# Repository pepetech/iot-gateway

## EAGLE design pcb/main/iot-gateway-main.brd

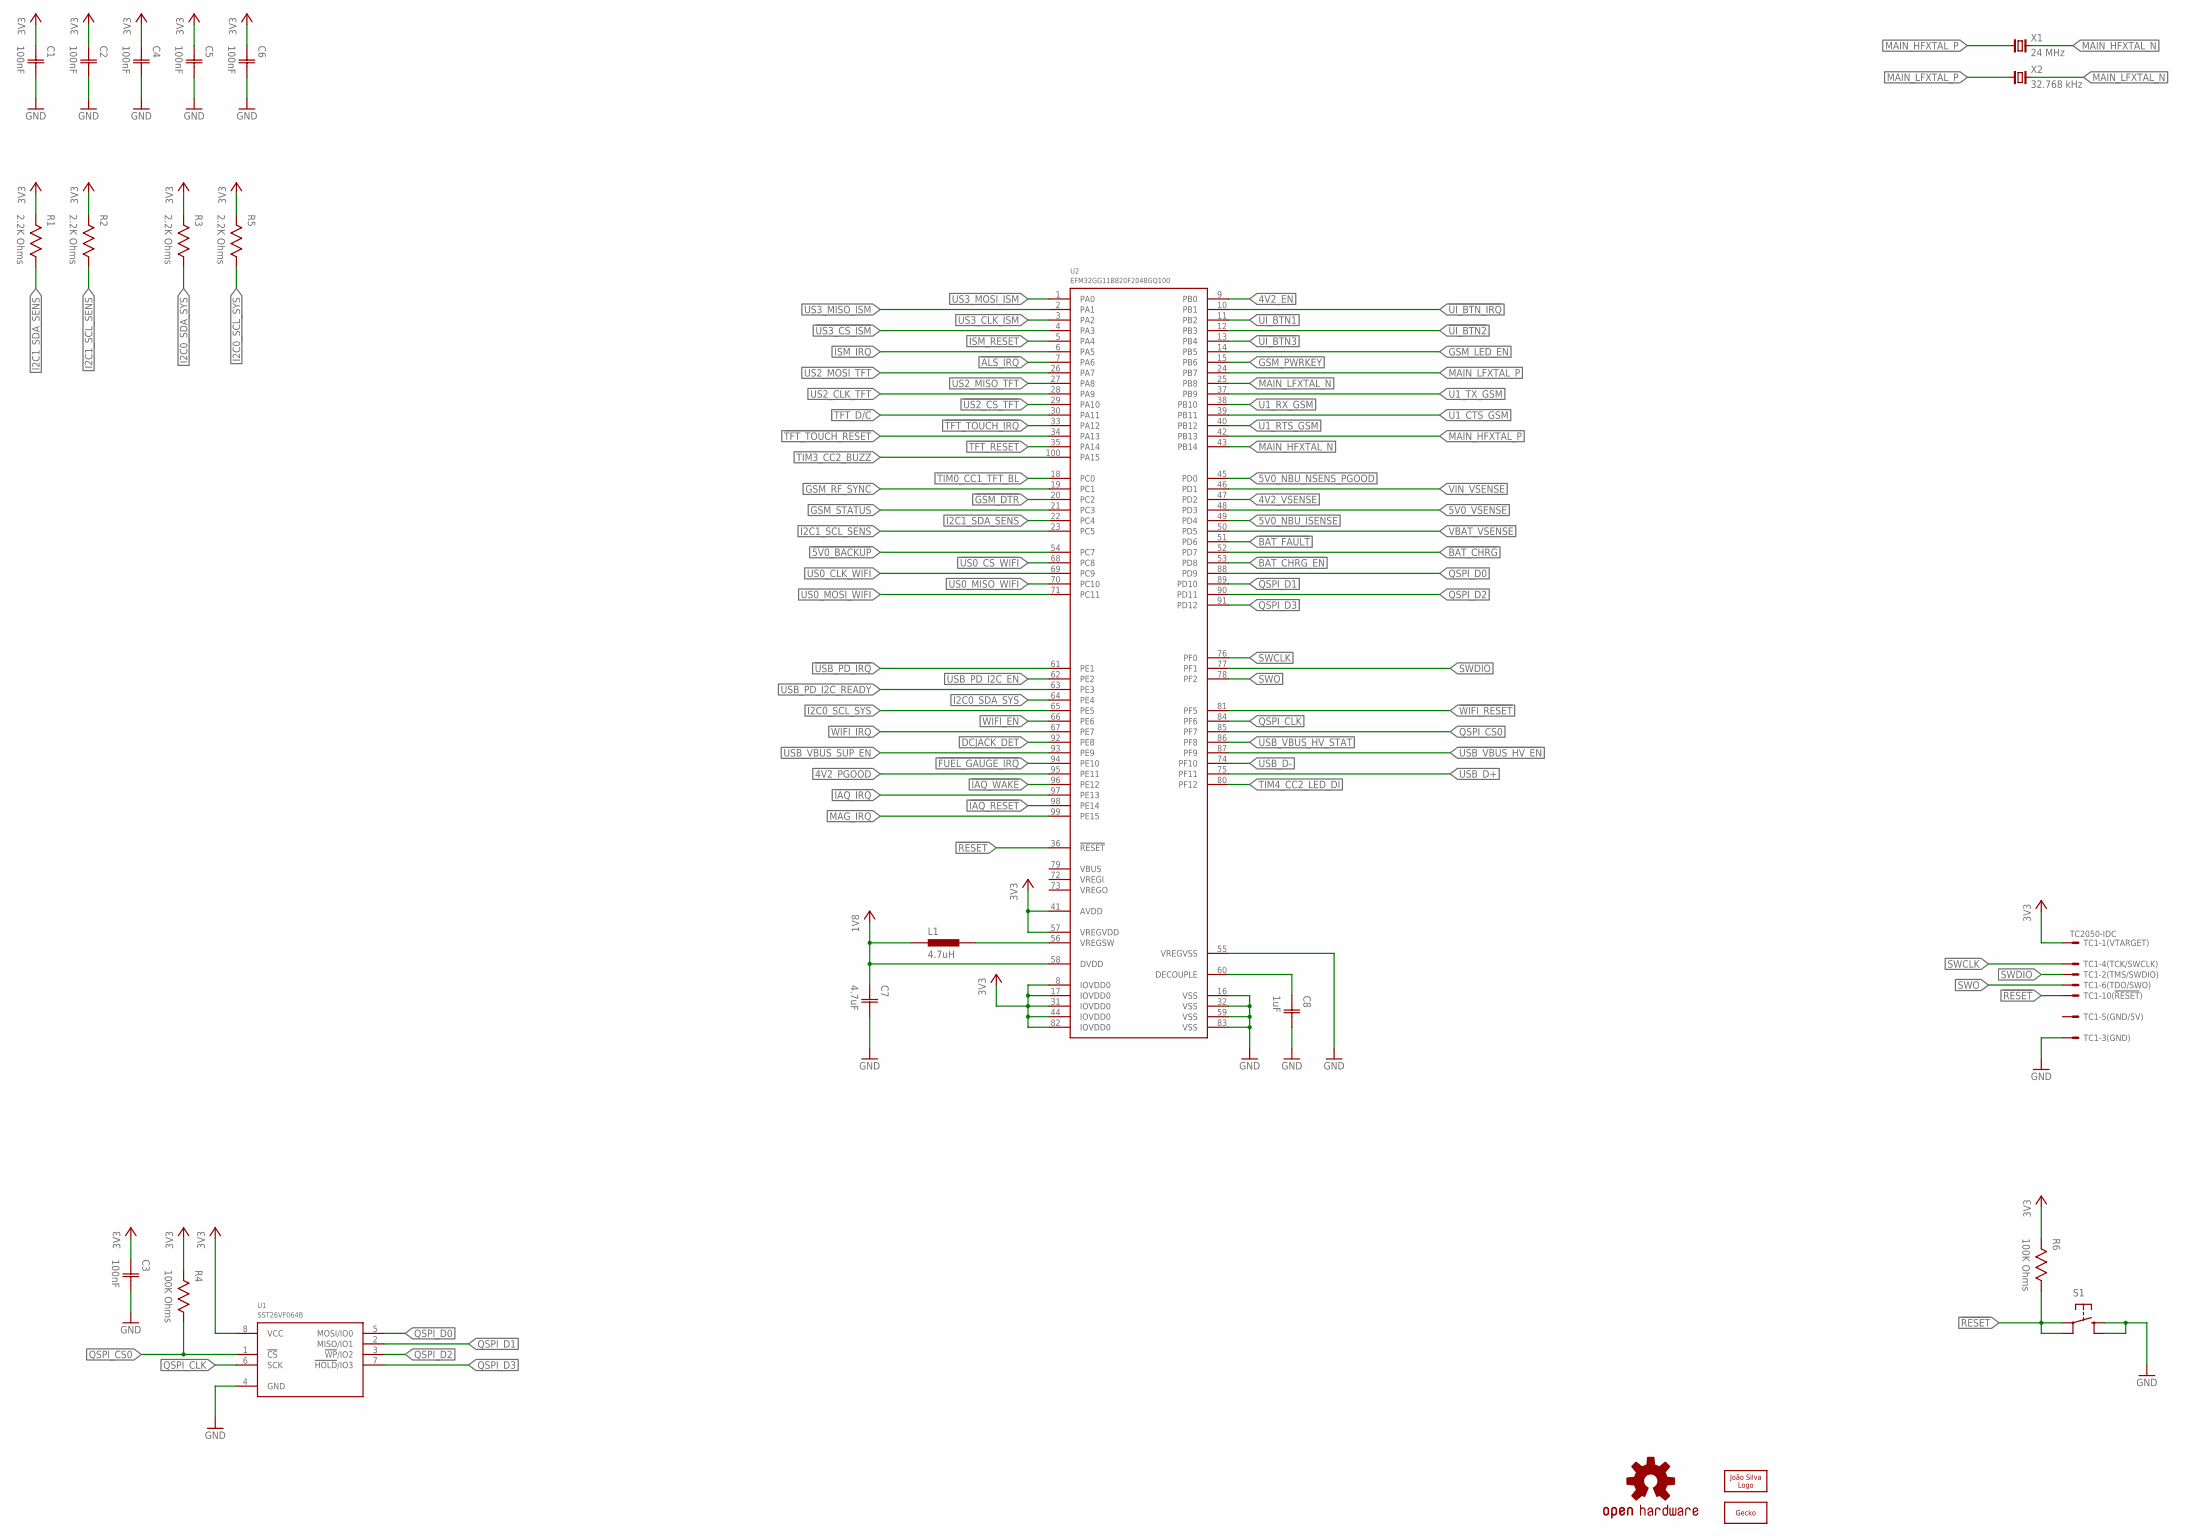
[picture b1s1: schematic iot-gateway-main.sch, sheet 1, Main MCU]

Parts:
C1, C2, C3, C4, C5, C6: 100nF; CAP0603
C7: 4.7uF; CAP0603
C8: 1uF; CAP0603
L1: 4.7uH; IND0603
LOGO1: OSHW-LOGOM; OSHW-LOGO-M
LOGO2: JS-10MM; JS_10MM
LOGO3: GECKO-14MM; GECKO_14MM
R1, R2, R3, R5: 2.2K Ohms; RES0603
R4, R6: 100K Ohms; RES0603
S1: TAC_SWITCHSMD; TAC_SW_SMD_RESET
TC1: TC2050-IDC
U1: SST26VF064B; WSOIC8
U2: EFM32GG11B820F2048GQ100; QFP100
X1: 24 MHz; 2-SMD-5032
X2: 32.768 kHz; 2-SMD-3215

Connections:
1V8: C7.1 (C1), L1.1, U2.58 (DVDD)
3V3: C1.1 (C1), C2.1 (C1), C3.1 (C1), C4.1 (C1), C5.1 (C1), C6.1 (C1), R1.2, R2.2, R3.2, R4.2, R5.2, R6.2, TC1.1, U1.8 (VCC), U2.8 (IOVDD0), U2.17 (IOVDD0), U2.31 (IOVDD0), U2.41 (AVDD), U2.44 (IOVDD0), U2.57 (VREGVDD), U2.82 (IOVDD0); also elsewhere on the board
4V2_EN: U2.9 (PB0); also elsewhere on the board
4V2_PGOOD: U2.95 (PE11); also elsewhere on the board
4V2_VSENSE: U2.47 (PD2); also elsewhere on the board
5V0_NBU_ISENSE: U2.49 (PD4); also elsewhere on the board
5V0_NBU_NSENS_PGOOD: U2.45 (PD0); also elsewhere on the board
5V0_VSENSE: U2.48 (PD3); also elsewhere on the board
!5V0_BACKUP: U2.54 (PC7); also elsewhere on the board
!ALS_IRQ: U2.7 (PA6); also elsewhere on the board
!BAT_CHRG: U2.52 (PD7); also elsewhere on the board
!BAT_CHRG_EN: U2.53 (PD8); also elsewhere on the board
!BAT_FAULT: U2.51 (PD6); also elsewhere on the board
!FUEL_GAUGE_IRQ: U2.94 (PE10); also elsewhere on the board
!GSM_DTR: U2.20 (PC2); also elsewhere on the board
!IAQ_IRQ: U2.97 (PE13); also elsewhere on the board
!IAQ_RESET: U2.98 (PE14); also elsewhere on the board
!IAQ_WAKE: U2.96 (PE12); also elsewhere on the board
!RESET: R6.1, S1.1, S1.2, TC1.10, U2.36 (!RESET)
!TFT_RESET: U2.35 (PA14); also elsewhere on the board
!TFT_TOUCH_IRQ: U2.33 (PA12); also elsewhere on the board
!TFT_TOUCH_RESET: U2.34 (PA13); also elsewhere on the board
!UI_BTN1: U2.11 (PB2); also elsewhere on the board
!UI_BTN2: U2.12 (PB3); also elsewhere on the board
!UI_BTN3: U2.13 (PB4); also elsewhere on the board
!UI_BTN_IRQ: U2.10 (PB1); also elsewhere on the board
!US0_CS_WIFI: U2.68 (PC8); also elsewhere on the board
!US2_CS_TFT: U2.29 (PA10); also elsewhere on the board
!US3_CS_ISM: U2.4 (PA3); also elsewhere on the board
!USB_PD_IRQ: U2.61 (PE1); also elsewhere on the board
!USB_VBUS_HV_EN: U2.87 (PF9); also elsewhere on the board
!WIFI_RESET: U2.81 (PF5); also elsewhere on the board
DCJACK_DET: U2.92 (PE8); also elsewhere on the board
GND: C1.2 (C2), C2.2 (C2), C3.2 (C2), C4.2 (C2), C5.2 (C2), C6.2 (C2), C7.2 (C2), C8.2 (C2), S1.3, S1.4, TC1.3, U1.4 (GND), U2.16 (VSS), U2.32 (VSS), U2.55 (VREGVSS), U2.59 (VSS), U2.83 (VSS); also elsewhere on the board
GSM_LED_EN: U2.14 (PB5); also elsewhere on the board
GSM_PWRKEY: U2.15 (PB6); also elsewhere on the board
GSM_RF_SYNC: U2.19 (PC1); also elsewhere on the board
GSM_STATUS: U2.21 (PC3); also elsewhere on the board
I2C0_SCL_SYS: R5.1, U2.65 (PE5); also elsewhere on the board
I2C0_SDA_SYS: R3.1, U2.64 (PE4); also elsewhere on the board
I2C1_SCL_SENS: R2.1, U2.23 (PC5); also elsewhere on the board
I2C1_SDA_SENS: R1.1, U2.22 (PC4); also elsewhere on the board
ISM_IRQ: U2.6 (PA5); also elsewhere on the board
ISM_RESET: U2.5 (PA4); also elsewhere on the board
MAG_IRQ: U2.99 (PE15); also elsewhere on the board
MAIN_HFXTAL_N: U2.43 (PB14), X1.2
MAIN_HFXTAL_P: U2.42 (PB13), X1.1
MAIN_LFXTAL_N: U2.25 (PB8), X2.2
MAIN_LFXTAL_P: U2.24 (PB7), X2.1
MAIN_VDD_CORE: C8.1 (C1), U2.60 (DECOUPLE)
MAIN_VREG_SW: L1.2, U2.56 (VREGSW)
QSPI_CLK: U1.6 (SCK), U2.84 (PF6)
QSPI_CS0: R4.1, U1.1 (!CS!), U2.85 (PF7)
QSPI_D0: U1.5 (MOSI/IO0), U2.88 (PD9)
QSPI_D1: U1.2 (MISO/IO1), U2.89 (PD10)
QSPI_D2: U1.3 (!WP!/IO2), U2.90 (PD11)
QSPI_D3: U1.7 (!HOLD!/IO3), U2.91 (PD12)
SWCLK: TC1.4, U2.76 (PF0)
SWDIO: TC1.2, U2.77 (PF1)
SWO: TC1.6, U2.78 (PF2)
TFT_D/!C!: U2.30 (PA11); also elsewhere on the board
TIM0_CC1_TFT_BL: U2.18 (PC0); also elsewhere on the board
TIM3_CC2_BUZZ: U2.100 (PA15); also elsewhere on the board
TIM4_CC2_LED_DI: U2.80 (PF12); also elsewhere on the board
U1_CTS_GSM: U2.39 (PB11); also elsewhere on the board
U1_RTS_GSM: U2.40 (PB12); also elsewhere on the board
U1_RX_GSM: U2.38 (PB10); also elsewhere on the board
U1_TX_GSM: U2.37 (PB9); also elsewhere on the board
US0_CLK_WIFI: U2.69 (PC9); also elsewhere on the board
US0_MISO_WIFI: U2.70 (PC10); also elsewhere on the board
US0_MOSI_WIFI: U2.71 (PC11); also elsewhere on the board
US2_CLK_TFT: U2.28 (PA9); also elsewhere on the board
US2_MISO_TFT: U2.27 (PA8); also elsewhere on the board
US2_MOSI_TFT: U2.26 (PA7); also elsewhere on the board
US3_CLK_ISM: U2.3 (PA2); also elsewhere on the board
US3_MISO_ISM: U2.2 (PA1); also elsewhere on the board
US3_MOSI_ISM: U2.1 (PA0); also elsewhere on the board
USB_D+: U2.75 (PF11); also elsewhere on the board
USB_D-: U2.74 (PF10); also elsewhere on the board
USB_PD_I2C_EN: U2.62 (PE2); also elsewhere on the board
USB_PD_I2C_READY: U2.63 (PE3); also elsewhere on the board
USB_VBUS_HV_STAT: U2.86 (PF8); also elsewhere on the board
USB_VBUS_SUP_EN: U2.93 (PE9); also elsewhere on the board
VBAT_VSENSE: U2.50 (PD5); also elsewhere on the board
VIN_VSENSE: U2.46 (PD1); also elsewhere on the board
WIFI_EN: U2.66 (PE6); also elsewhere on the board
WIFI_IRQ: U2.67 (PE7); also elsewhere on the board

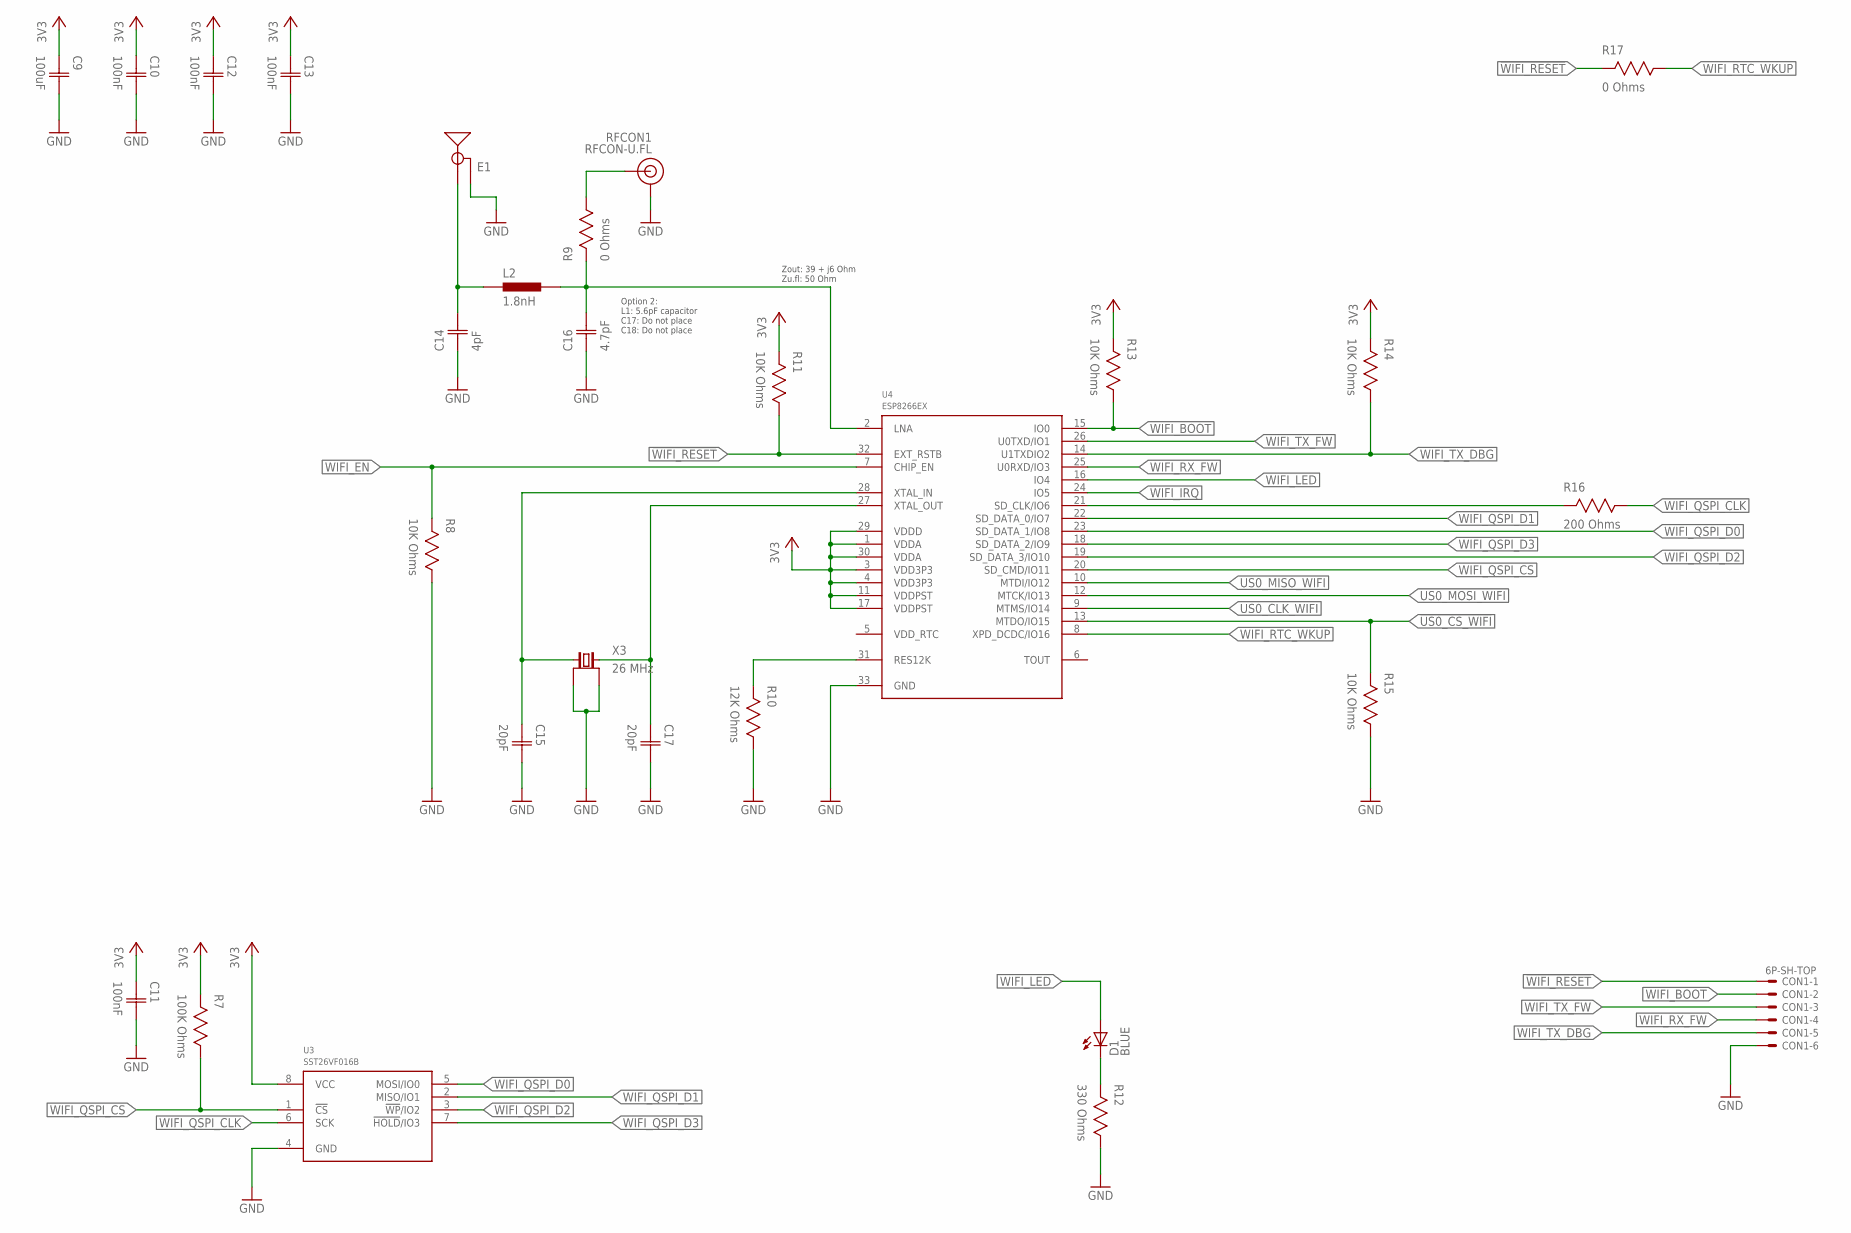
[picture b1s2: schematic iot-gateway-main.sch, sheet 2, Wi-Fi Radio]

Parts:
C9: 100uF; CAP1206
C10, C11, C12, C13: 100nF; CAP0603
C14: 4pF; CAP0603
C15, C17: 20pF; CAP0603
C16: 4.7pF; CAP0603
CON1: 6P-SH-TOP; SH-06-TOP
D1: BLUE; 1206_REV
E1: 2.4GHZTRACE-15.2MM; TRACE_ANTENNA_2.4GHZ_15.2MM
L2: 1.8nH; IND0603
R7: 100K Ohms; RES0603
R8, R11, R13, R14, R15: 10K Ohms; RES0603
R9, R17: 0 Ohms; RES0603
R10: 12K Ohms; RES0603
R12: 330 Ohms; RES0603
R16: 200 Ohms; RES0603
RFCON1: RFCON-U.FL; U.FL
U3: SST26VF016B; WSOIC8
U4: ESP8266EX; QFN32
X3: 26 MHz; 4-SMD-3225

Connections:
3V3: C9.1 (C1), C10.1 (C1), C11.1 (C1), C12.1 (C1), C13.1 (C1), R7.2, R11.2, R13.2, R14.2, U3.8 (VCC), U4.1 (VDDA), U4.3 (VDD3P3), U4.4 (VDD3P3), U4.11 (VDDPST), U4.17 (VDDPST), U4.29 (VDDD), U4.30 (VDDA); also elsewhere on the board
!US0_CS_WIFI: R15.2, U4.13 (MTDO/IO15); also elsewhere on the board
!WIFI_RESET: CON1.1, R11.1, R17.2, U4.32 (EXT_RSTB); also elsewhere on the board
GND: C9.2 (C2), C10.2 (C2), C11.2 (C2), C12.2 (C2), C13.2 (C2), C14.1 (C1), C15.2 (C2), C16.1 (C1), C17.2 (C2), CON1.6, E1.GND, R8.1, R10.1, R12.1, R15.1, RFCON1.P$1 (GND), RFCON1.P$2 (GND), U3.4 (GND), U4.33 (GND), X3.1 (GND), X3.3 (GND); also elsewhere on the board
unnamed: D1.C, R12.2
US0_CLK_WIFI: U4.9 (MTMS/IO14); also elsewhere on the board
US0_MISO_WIFI: U4.10 (MTDI/IO12); also elsewhere on the board
US0_MOSI_WIFI: U4.12 (MTCK/IO13); also elsewhere on the board
WIFI_ANT: C16.2 (C2), L2.2, R9.2, U4.2 (LNA)
WIFI_ANT_EXT: R9.1, RFCON1.P$3 (SIGNAL)
WIFI_ANT_FILT: C14.2 (C2), E1.ANT (SIGNAL), L2.1
WIFI_BIAS: R10.2, U4.31 (RES12K)
WIFI_BOOT: CON1.2, R13.1, U4.15 (IO0)
WIFI_EN: R8.2, U4.7 (CHIP_EN); also elsewhere on the board
WIFI_IRQ: U4.24 (IO5); also elsewhere on the board
WIFI_LED: D1.A, U4.16 (IO4)
WIFI_QSPI_CLK: R16.1, U3.6 (SCK)
WIFI_QSPI_CLK_FILT: R16.2, U4.21 (SD_CLK/IO6)
WIFI_QSPI_CS: R7.1, U3.1 (!CS!), U4.20 (SD_CMD/IO11)
WIFI_QSPI_D0: U3.5 (MOSI/IO0), U4.23 (SD_DATA_1/IO8)
WIFI_QSPI_D1: U3.2 (MISO/IO1), U4.22 (SD_DATA_0/IO7)
WIFI_QSPI_D2: U3.3 (!WP!/IO2), U4.19 (SD_DATA_3/IO10)
WIFI_QSPI_D3: U3.7 (!HOLD!/IO3), U4.18 (SD_DATA_2/IO9)
WIFI_RTC_WKUP: R17.1, U4.8 (XPD_DCDC/IO16)
WIFI_RX_FW: CON1.4, U4.25 (U0RXD/IO3)
WIFI_TX_DBG: CON1.5, R14.1, U4.14 (U1TXDIO2)
WIFI_TX_FW: CON1.3, U4.26 (U0TXD/IO1)
WIFI_XTAL_IN: C15.1 (C1), U4.28 (XTAL_IN), X3.2 (1)
WIFI_XTAL_OUT: C17.1 (C1), U4.27 (XTAL_OUT), X3.4 (2)

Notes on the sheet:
Option 2: L1: 5.6pF capacitor C17: Do not place C18: Do not place
Zout: 39 + j6 Ohm Zu.fl: 50 Ohm

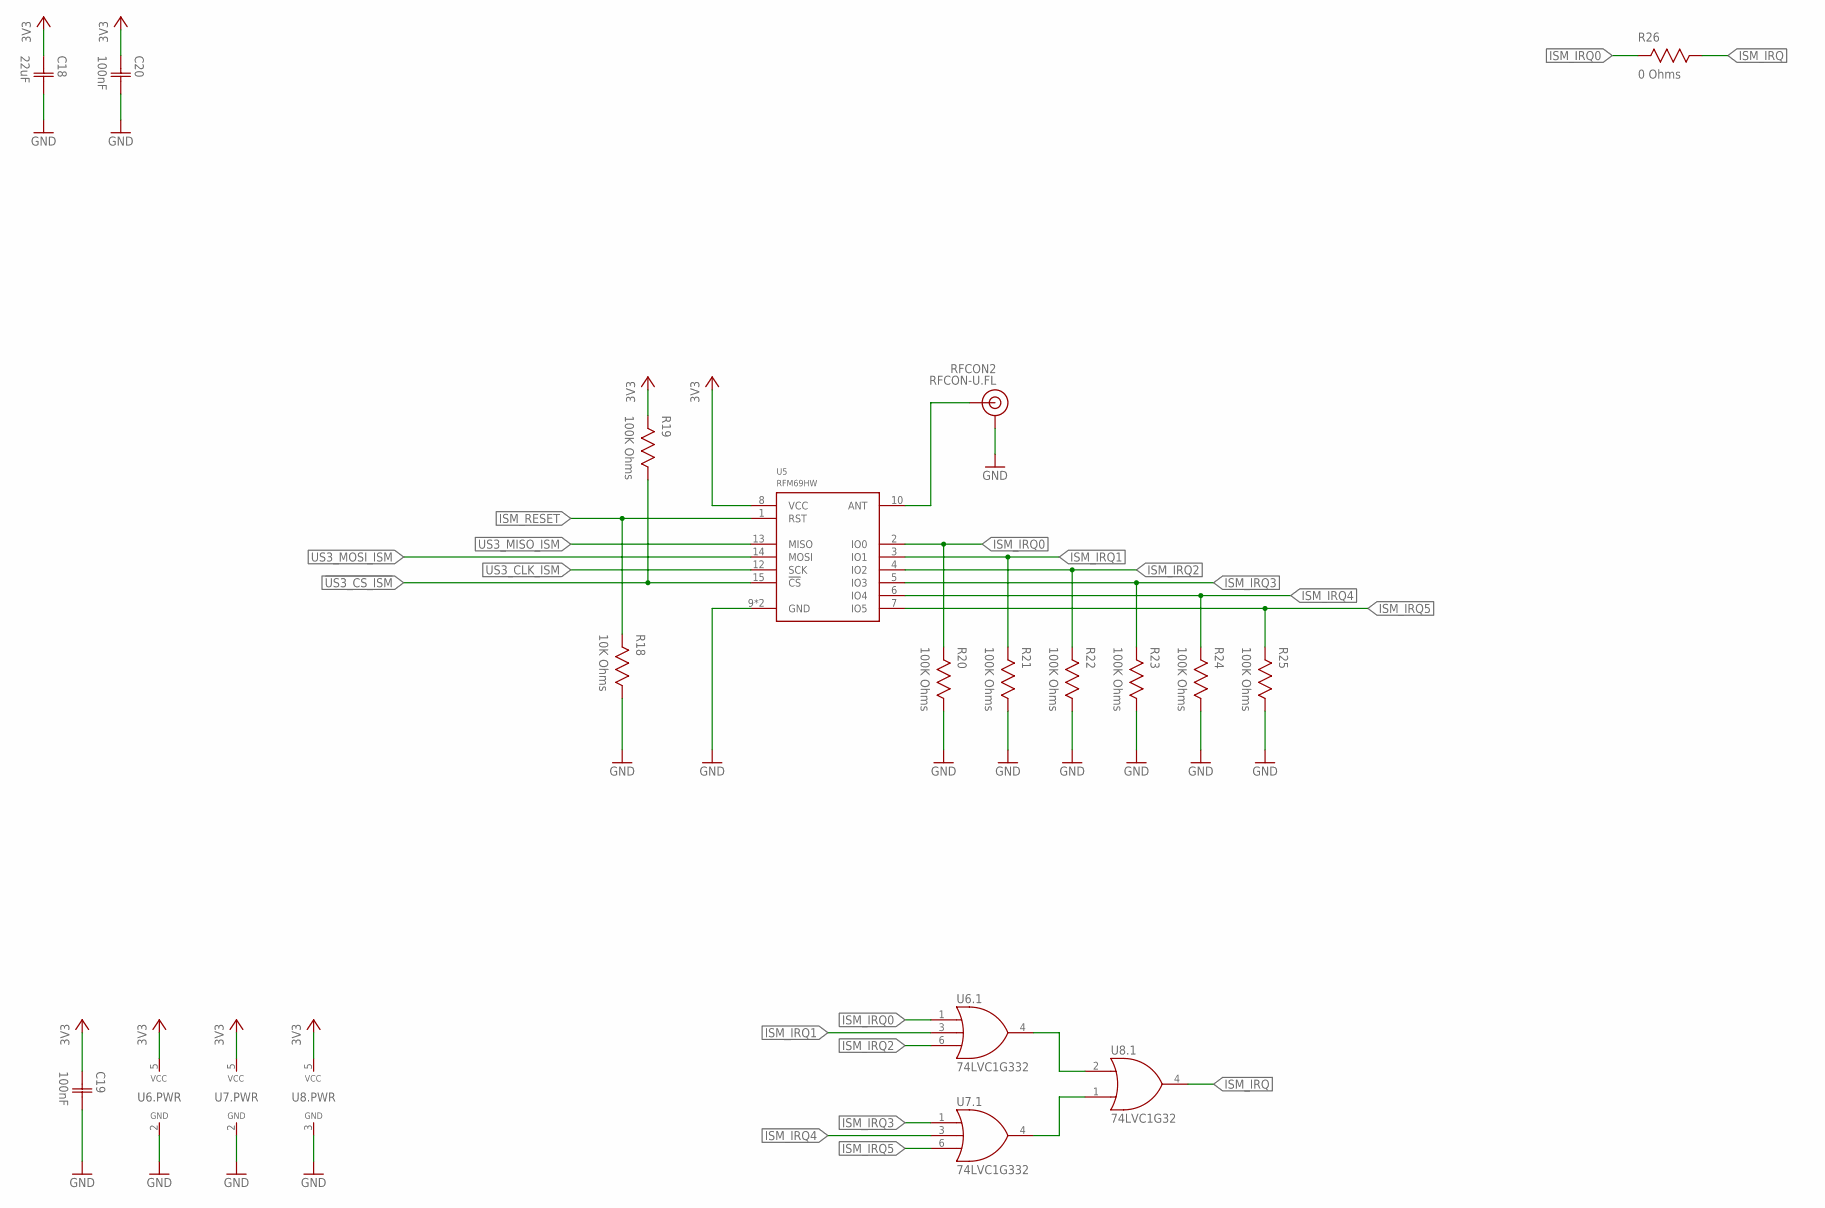
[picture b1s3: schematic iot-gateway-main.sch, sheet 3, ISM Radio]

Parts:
C18: 22uF; CAP1206
C19, C20: 100nF; CAP0603
R18: 10K Ohms; RES0603
R19, R20, R21, R22, R23, R24, R25: 100K Ohms; RES0603
R26: 0 Ohms; RES0603
RFCON2: RFCON-U.FL; U.FL
U5: RFM69HW; RFM69XW-XXXS2
U6, U7: 74LVC1G332; SC70-6
U8: 74LVC1G32; SC70-5

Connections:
3V3: C18.1 (C1), C19.1 (C1), C20.1 (C1), R19.2, U5.8 (VCC), U6.5 (VCC), U7.5 (VCC), U8.5 (VCC); also elsewhere on the board
!US3_CS_ISM: R19.1, U5.15 (!CS); also elsewhere on the board
GND: C18.2 (C2), C19.2 (C2), C20.2 (C2), R18.1, R20.1, R21.1, R22.1, R23.1, R24.1, R25.1, RFCON2.P$1 (GND), RFCON2.P$2 (GND), U5.9 (GND), U5.11 (GND), U6.2 (GND), U7.2 (GND), U8.3 (GND); also elsewhere on the board
ISM_IRQ: R26.1, U8.4 (Y); also elsewhere on the board
ISM_IRQ0: R20.2, R26.2, U5.2 (IO0), U6.1 (A)
ISM_IRQ1: R21.2, U5.3 (IO1), U6.3 (B)
ISM_IRQ2: R22.2, U5.4 (IO2), U6.6 (C)
ISM_IRQ3: R23.2, U5.5 (IO3), U7.1 (A)
ISM_IRQ4: R24.2, U5.6 (IO4), U7.3 (B)
ISM_IRQ5: R25.2, U5.7 (IO5), U7.6 (C)
ISM_IRQ012: U6.4 (Y), U8.2 (A)
ISM_IRQ345: U7.4 (Y), U8.1 (B)
ISM_RESET: R18.2, U5.1 (RST); also elsewhere on the board
unnamed: RFCON2.P$3 (SIGNAL), U5.10 (ANT)
US3_CLK_ISM: U5.12 (SCK); also elsewhere on the board
US3_MISO_ISM: U5.13 (MISO); also elsewhere on the board
US3_MOSI_ISM: U5.14 (MOSI); also elsewhere on the board

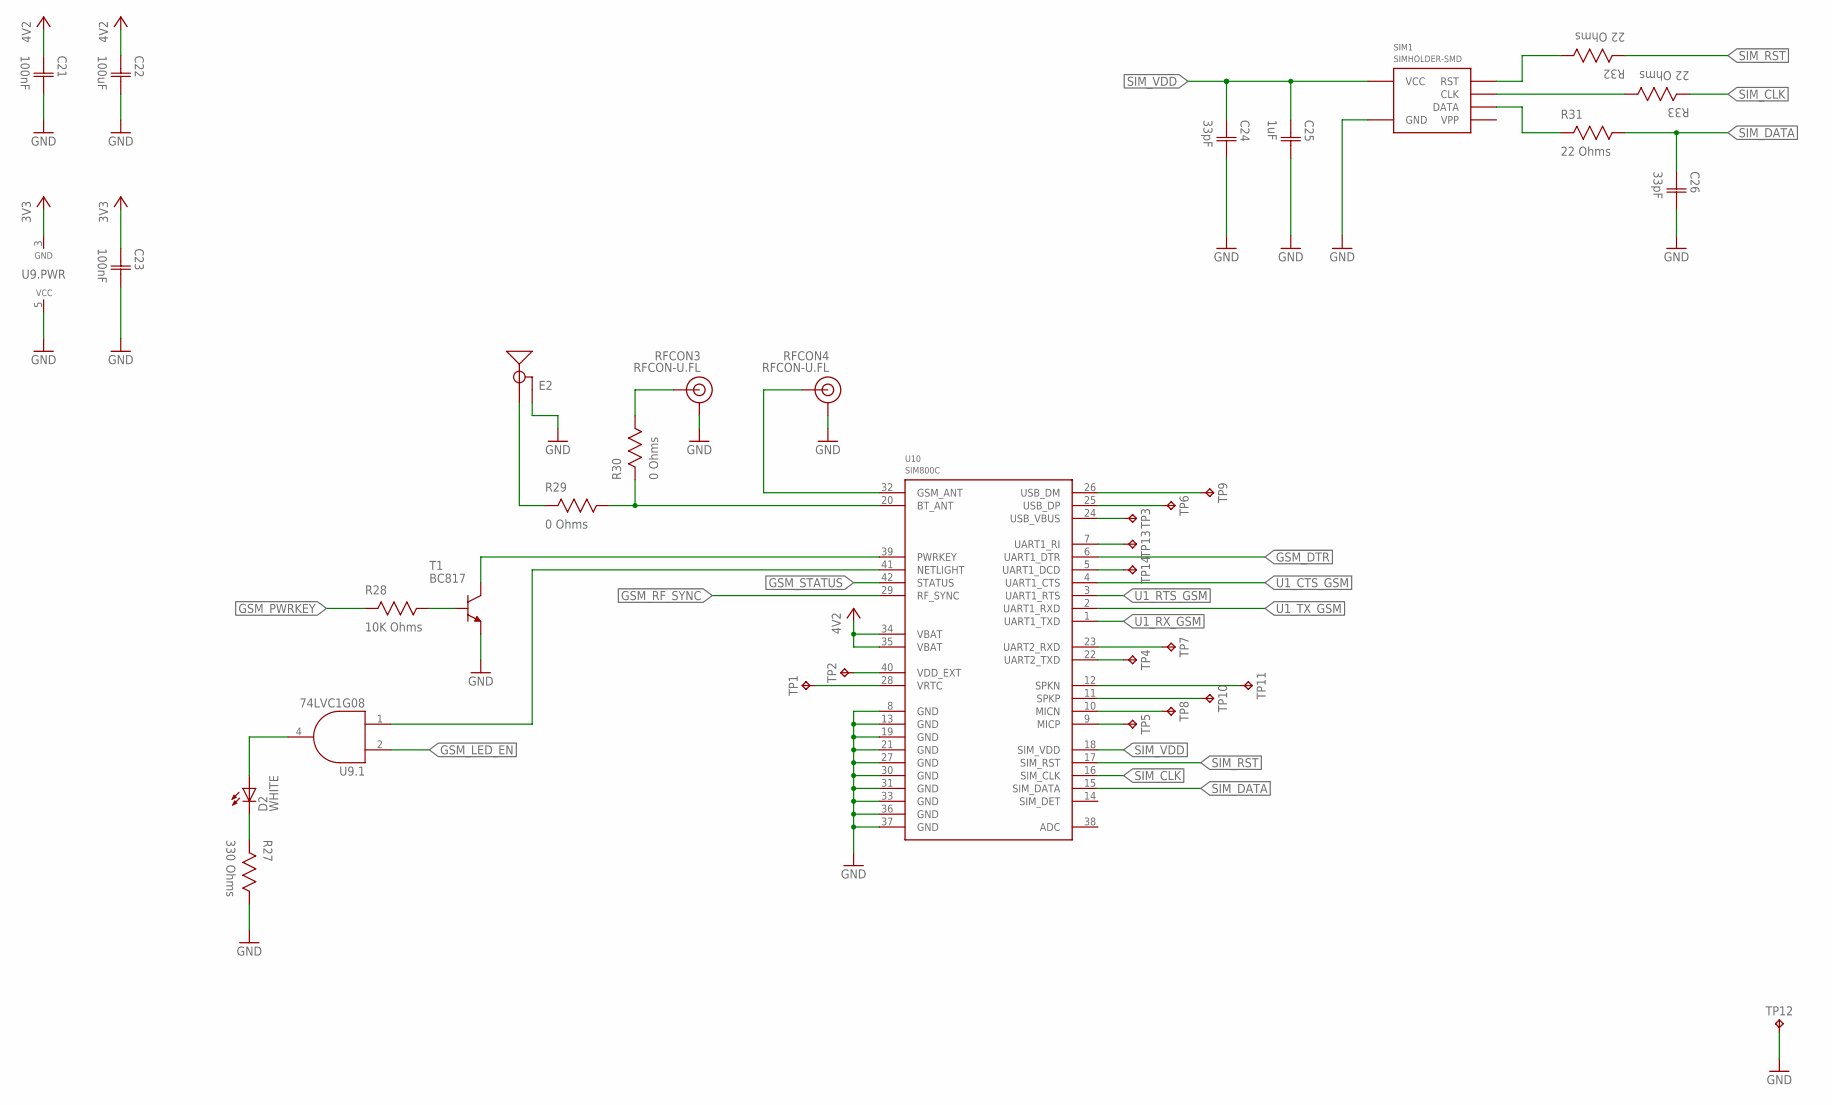
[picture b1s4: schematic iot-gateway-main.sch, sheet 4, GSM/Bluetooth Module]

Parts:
C21, C23: 100nF; CAP0603
C22: 100uF; CAP1206
C24, C26: 33pF; CAP0603
C25: 1uF; CAP0603
D2: WHITE; 1206_REV
E2: 2.4GHZTRACE-15.2MM; TRACE_ANTENNA_2.4GHZ_15.2MM
R27: 330 Ohms; RES0603
R28: 10K Ohms; RES0603
R29, R30: 0 Ohms; RES0603
R31, R32, R33: 22 Ohms; RES0603
RFCON3, RFCON4: RFCON-U.FL; U.FL
SIM1: SIMHOLDER-SMD
T1: BC817; SOT23
TP1, TP2, TP3, TP4, TP5, TP6, TP7, TP8, TP9, TP10, TP11, TP12, TP13, TP14: TESTPOINT-1.27MM; PAD1.27MM
U9: 74LVC1G08; SC70-5
U10: SIM800C

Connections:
3V3: C23.1 (C1), U9.3 (GND); also elsewhere on the board
4V2: C21.1 (C1), C22.1 (C1), U10.34 (VBAT), U10.35 (VBAT); also elsewhere on the board
!GSM_DCD: TP14.TP, U10.5 (UART1_DCD)
!GSM_DTR: U10.6 (UART1_DTR); also elsewhere on the board
!GSM_PWRKEY: T1.3 (C), U10.39 (PWRKEY)
!GSM_RING: TP13.TP, U10.7 (UART1_RI)
BT_ANT: R29.1, R30.2, U10.20 (BT_ANT)
BT_ANT_EXT: R30.1, RFCON3.P$3 (SIGNAL)
BT_ANT_INT: E2.ANT (SIGNAL), R29.2
GND: C21.2 (C2), C22.2 (C2), C23.2 (C2), C24.2 (C2), C25.2 (C2), C26.2 (C2), E2.GND, R27.1, RFCON3.P$1 (GND), RFCON3.P$2 (GND), RFCON4.P$1 (GND), RFCON4.P$2 (GND), SIM1.C5 (GND), T1.2 (E), TP12.TP, U9.5 (VCC), U10.8 (GND), U10.13 (GND), U10.19 (GND), U10.21 (GND), U10.27 (GND), U10.30 (GND), U10.31 (GND), U10.33 (GND), U10.36 (GND), U10.37 (GND); also elsewhere on the board
GSM_2V8: TP2.TP, U10.40 (VDD_EXT)
GSM_ANT: RFCON4.P$3 (SIGNAL), U10.32 (GSM_ANT)
GSM_LED: D2.A, U9.4 (Y)
GSM_LED_EN: U9.2 (A); also elsewhere on the board
GSM_MIC+: TP5.TP, U10.9 (MICP)
GSM_MIC-: TP8.TP, U10.10 (MICN)
GSM_NETLIGHT: U9.1 (B), U10.41 (NETLIGHT)
GSM_PWRKEY: R28.2; also elsewhere on the board
GSM_RF_SYNC: U10.29 (RF_SYNC); also elsewhere on the board
GSM_SPK+: TP10.TP, U10.11 (SPKP)
GSM_SPK-: TP11.TP, U10.12 (SPKN)
GSM_STATUS: U10.42 (STATUS); also elsewhere on the board
GSM_UART2_RX: TP7.TP, U10.23 (UART2_RXD)
GSM_UART2_TX: TP4.TP, U10.22 (UART2_TXD)
GSM_USB_D+: TP6.TP, U10.25 (USB_DP)
GSM_USB_D-: TP9.TP, U10.26 (USB_DM)
GSM_USB_VBUS: TP3.TP, U10.24 (USB_VBUS)
GSM_VRTC: TP1.TP, U10.28 (VRTC)
unnamed: D2.C, R27.2
unnamed: R28.1, T1.1 (B)
SIM_CLK: R33.2, U10.16 (SIM_CLK)
SIM_CLK_FILT: R33.1, SIM1.C3 (CLK)
SIM_DATA: C26.1 (C1), R31.1, U10.15 (SIM_DATA)
SIM_DATA_FILT: R31.2, SIM1.C7 (DATA)
SIM_RST: R32.2, U10.17 (SIM_RST)
SIM_RST_FILT: R32.1, SIM1.C2 (RST)
SIM_VDD: C24.1 (C1), C25.1 (C1), SIM1.C1 (VCC), U10.18 (SIM_VDD)
U1_CTS_GSM: U10.4 (UART1_CTS); also elsewhere on the board
U1_RTS_GSM: U10.3 (UART1_RTS); also elsewhere on the board
U1_RX_GSM: U10.1 (UART1_TXD); also elsewhere on the board
U1_TX_GSM: U10.2 (UART1_RXD); also elsewhere on the board

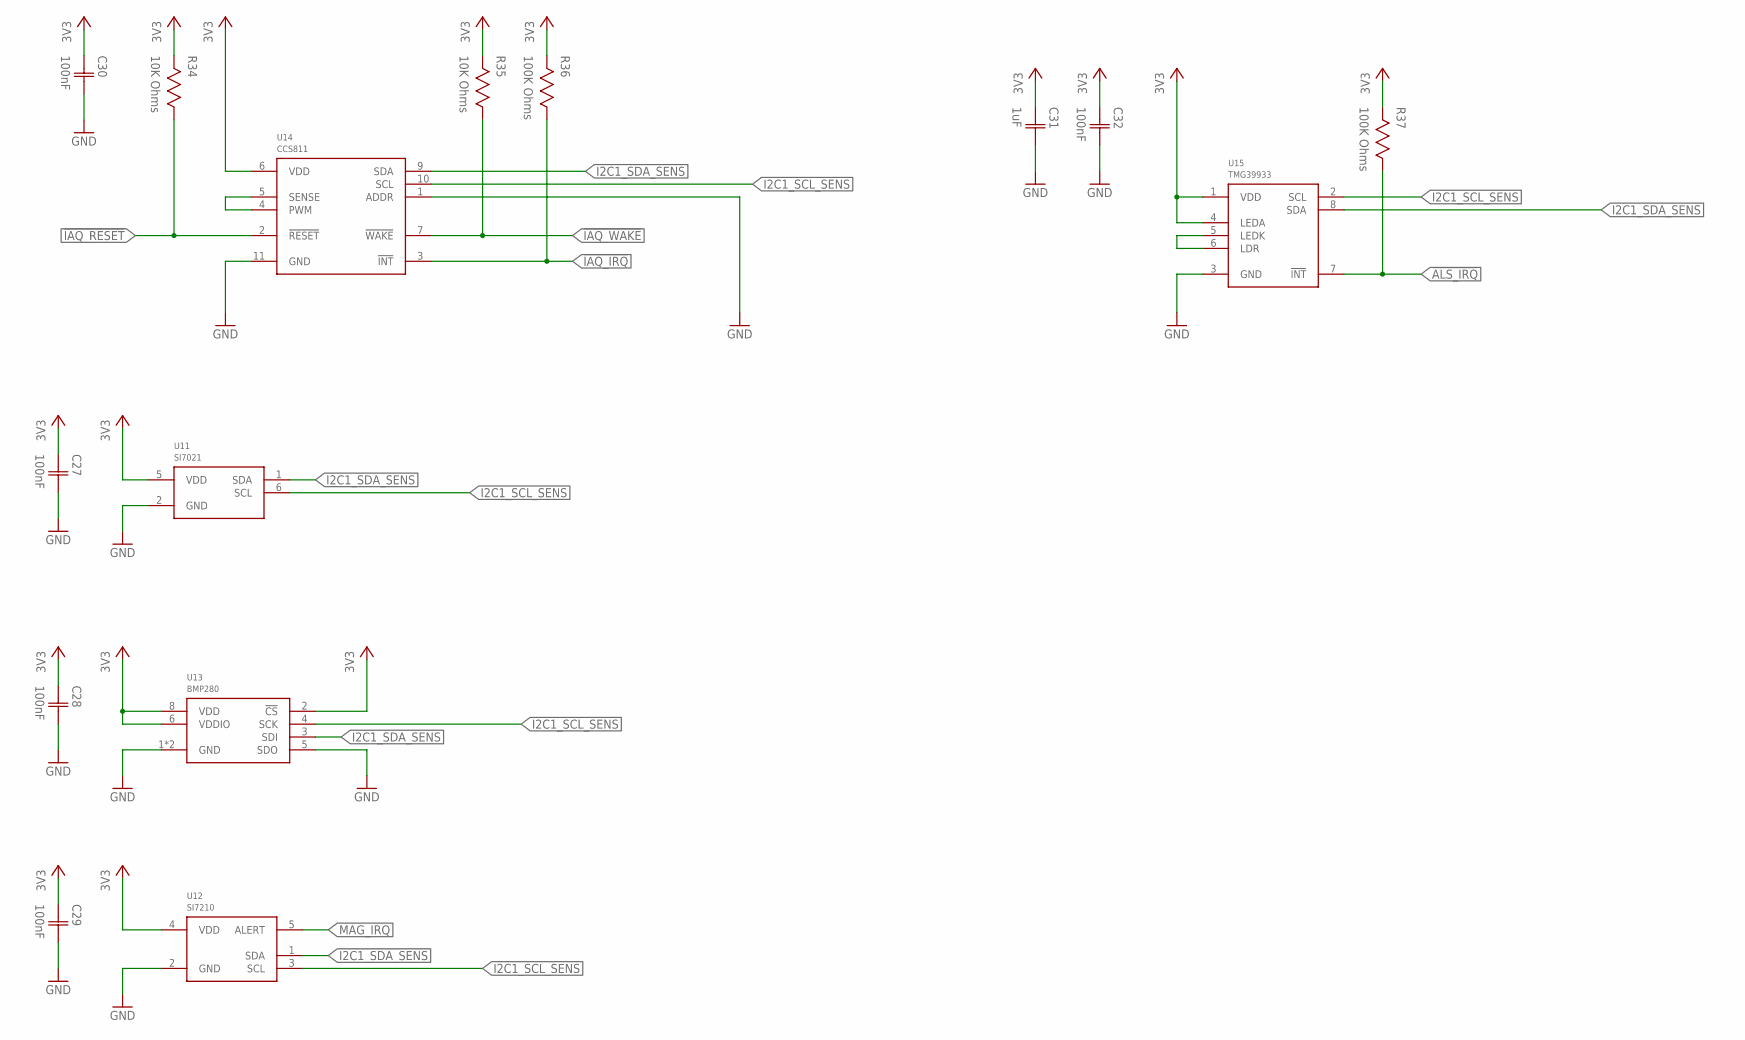
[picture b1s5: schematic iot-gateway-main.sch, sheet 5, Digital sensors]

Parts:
C27, C28, C29, C30, C32: 100nF; CAP0603
C31: 1uF; CAP0603
R34, R35: 10K Ohms; RES0603
R36, R37: 100K Ohms; RES0603
U11: SI7021; DFN6
U12: SI7210; SOT23-5
U13: BMP280
U14: CCS811; LGA10
U15: TMG39933; LGA8

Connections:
3V3: C27.1 (C1), C28.1 (C1), C29.1 (C1), C30.1 (C1), C31.1 (C1), C32.1 (C1), R34.2, R35.2, R36.2, R37.2, U11.5 (VDD), U12.4 (VDD), U13.2 (!CS), U13.6 (VDDIO), U13.8 (VDD), U14.6 (VDD), U15.1 (VDD), U15.4 (LEDA); also elsewhere on the board
!ALS_IRQ: R37.1, U15.7 (!INT); also elsewhere on the board
!IAQ_IRQ: R36.1, U14.3 (!INT); also elsewhere on the board
!IAQ_RESET: R34.1, U14.2 (!RESET); also elsewhere on the board
!IAQ_WAKE: R35.1, U14.7 (!WAKE); also elsewhere on the board
CCS811_HEATER_PWM: U14.4 (PWM), U14.5 (SENSE)
GND: C27.2 (C2), C28.2 (C2), C29.2 (C2), C30.2 (C2), C31.2 (C2), C32.2 (C2), U11.2 (GND), U12.2 (GND), U13.1 (GND), U13.5 (SDO), U13.7 (GND), U14.1 (ADDR), U14.11 (GND), U15.3 (GND); also elsewhere on the board
I2C1_SCL_SENS: U11.6 (SCL), U12.3 (SCL), U13.4 (SCK), U14.10 (SCL), U15.2 (SCL); also elsewhere on the board
I2C1_SDA_SENS: U11.1 (SDA), U12.1 (SDA), U13.3 (SDI), U14.9 (SDA), U15.8 (SDA); also elsewhere on the board
MAG_IRQ: U12.5 (ALERT); also elsewhere on the board
unnamed: U15.5 (LEDK), U15.6 (LDR)

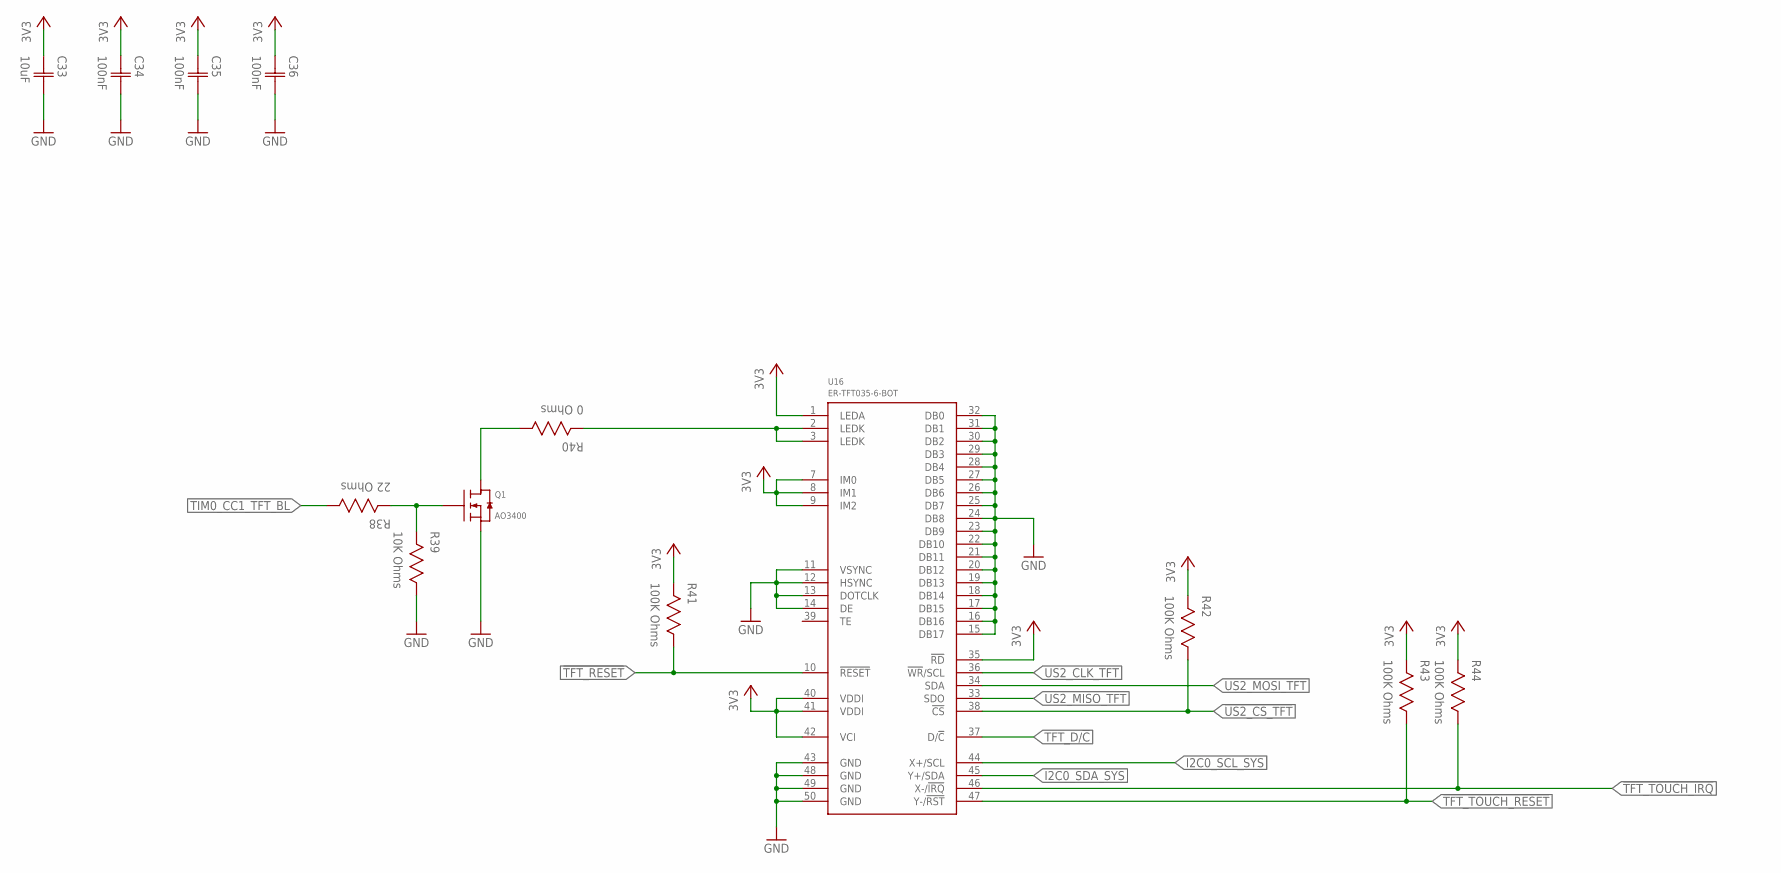
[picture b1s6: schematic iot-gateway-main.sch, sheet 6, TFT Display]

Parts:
C33: 10uF; CAP0603
C34, C35, C36: 100nF; CAP0603
Q1: AO3400; SOT23
R38: 22 Ohms; RES0603
R39: 10K Ohms; RES0603
R40: 0 Ohms; RES0603
R41, R42, R43, R44: 100K Ohms; RES0603
U16: ER-TFT035-6-BOT; FPC-50P-TFT-BOT

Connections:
3V3: C33.1 (C1), C34.1 (C1), C35.1 (C1), C36.1 (C1), R41.2, R42.2, R43.2, R44.2, U16.1 (LEDA), U16.7 (IM0), U16.8 (IM1), U16.9 (IM2), U16.35 (!RD), U16.40 (VDDI), U16.41 (VDDI), U16.42 (VCI); also elsewhere on the board
!TFT_RESET: R41.1, U16.10 (!RESET); also elsewhere on the board
!TFT_TOUCH_IRQ: R44.1, U16.46 (X-/!IRQ!); also elsewhere on the board
!TFT_TOUCH_RESET: R43.1, U16.47 (Y-/!RST!); also elsewhere on the board
!US2_CS_TFT: R42.1, U16.38 (!CS); also elsewhere on the board
GND: C33.2 (C2), C34.2 (C2), C35.2 (C2), C36.2 (C2), Q1.2 (S), R39.1, U16.11 (VSYNC), U16.12 (HSYNC), U16.13 (DOTCLK), U16.14 (DE), U16.15 (DB17), U16.16 (DB16), U16.17 (DB15), U16.18 (DB14), U16.19 (DB13), U16.20 (DB12), U16.21 (DB11), U16.22 (DB10), U16.23 (DB9), U16.24 (DB8), U16.25 (DB7), U16.26 (DB6), U16.27 (DB5), U16.28 (DB4), U16.29 (DB3), U16.30 (DB2), U16.31 (DB1), U16.32 (DB0), U16.43 (GND), U16.48 (GND), U16.49 (GND), U16.50 (GND); also elsewhere on the board
I2C0_SCL_SYS: U16.44 (X+/SCL); also elsewhere on the board
I2C0_SDA_SYS: U16.45 (Y+/SDA); also elsewhere on the board
unnamed: Q1.1 (G), R38.2, R39.2
TFT_BACKLIGHT_DRIVER: Q1.3 (D), R40.1
TFT_BACKLIGHT_PWM: R40.2, U16.2 (LEDK), U16.3 (LEDK)
TFT_D/!C!: U16.37 (D/!C!); also elsewhere on the board
TIM0_CC1_TFT_BL: R38.1; also elsewhere on the board
US2_CLK_TFT: U16.36 (!WR!/SCL); also elsewhere on the board
US2_MISO_TFT: U16.33 (SDO); also elsewhere on the board
US2_MOSI_TFT: U16.34 (SDA); also elsewhere on the board
